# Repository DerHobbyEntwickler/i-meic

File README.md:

# i-meic

*(German version: [README_de.md](README_de.md))*

**The i-meic is a modular, expandable single-board computer based on the Intel 8088 CPU.**

> The hardware aims to recreate an IBM PC using the simplest possible means.
> The PC compute core consists of the 8088 CPU and 1 MB of main memory.
> All input/output is handled by a Raspberry Pi RP2040 Pro Micro.
> That is faster, simpler and cheaper than classic peripheral chips.

---

## What does "i-meic" mean?

The name is derived from the German description of the project:

| Letter | Meaning  |
|--------|-----------|
| **i** | (**i**)ntel 8088 |
| **m** | (**m**)odular|
| **e** | (**e**)xpandable |
| **i** | s(**i**)ngle-board |
| **c** | (**c**)omputer |

---

## Concept in brief

Classic 8088 systems require a large number of peripheral chips
(clock generator, bus drivers, interrupt controller, DMA, floppy/HDD
controller, video, keyboard, etc.). The i-meic replaces this entire set of
peripherals with **a single microcontroller**: the Raspberry Pi Pico.

**The PC compute core consists of:**

- **1× Intel 8088 CPU** (16-bit, 20 address lines)
- **2× SRAM of 512 KByte each** → together **1 MByte** (the maximum of the
  8088 address space)

**The Raspberry Pi RP2040 Pro Micro (ARM Cortex-M0+) takes care of:**

- **clock generation** for the 8088 CPU (single-step / clocked operation)
- **loading the BIOS** into SRAM at startup
- the **complete I/O processing** (every read/write access to an I/O port
  is intercepted and serviced by the Pico)
- the **serial connection** to a host PC (screen, keyboard and drives are
  virtualized over the console)
- the **ITP3 interface** for modular expansion

This architecture is unusually powerful because the Pico runs at a
significantly higher clock frequency than the historic 8088 peripherals and
can therefore handle I/O operations very quickly.

---

## System and data flow

This is how a runnable DOS computer is created from source code:

```
   ┌────────────────────────────────────────────────────────────────┐
   │  70_RON-BIOS-NASM …  BIOS.ASM  (8088 assembler, NASM)          │
   │        │  nasm -f bin                                          │
   │        ▼                                                       │
   │     BIOS.BIN  (pure 8088 binary BIOS, segment F800:0000)       │
   │        │  COM2INC  (see 60_FPC_Lazarus/25_LAZ_CLI64_COM2INC)   │
   │        ▼                                                       │
   │     BIOS.INC  (Pascal byte array  BIOS_ARR[…])                 │
   └────────┬───────────────────────────────────────────────────────┘
            │  gets embedded into the Pico firmware
            ▼
   ┌────────────────────────────────────────────────────────────────┐
   │  10_…/20_Lazarus_PICO…  Firmware (Free Pascal / RP2040)        │
   │        │  Lazarus / FPC                                        │
   │        ▼                                                       │
   │     imeic_dos.uf2   →   flash onto the Raspberry Pi Pico       │
   └────────┬───────────────────────────────────────────────────────┘
            │  Pico boots:
            │  1. loads BIOS_ARR into SRAM (F800:0000)
            │  2. clocks the 8088 CPU
            │  3. services all I/O requests (IORQ)
            ▼
   ┌────────────────────────────────────────────────────────────────┐
   │  i-meic board  (8088 + 2×512 KB SRAM)  ←── serial ───┐         │
   └──────────────────────────────────────────────────────┼─────────┘
                                                           │ UART 921600 Bd
   ┌───────────────────────────────────────────────────────▼────────┐
   │  60_…/20_LAZ_Console64 …  CONSOLE64  (host PC, Win64/Linux)    │
   │  provides screen, keyboard and drive images:                  │
   │    BOOTA.IMG  (1.44 MB floppy)     BOOTC.IMG  (8 MB hard disk) │
   └────────────────────────────────────────────────────────────────┘
```

---

## Repository structure

| Folder | Contents |
|--------|--------|
| [`10_i-meic-pico_V6/`](10_i-meic-pico_V6/) | The actual i-meic board: KiCAD hardware **and** Pico firmware (ARM cross-compiler, I/O interface for DOS) |
| [`10_i-meic-pico_V6/10_KiCAD/`](10_i-meic-pico_V6/10_KiCAD/) | KiCAD project, schematic, layout, Gerber data for PCB manufacturing |
| [`10_i-meic-pico_V6/20_Lazarus_PICO_i-meic-pico_V6_DOS/`](10_i-meic-pico_V6/20_Lazarus_PICO_i-meic-pico_V6_DOS/) | Source code of the Pico firmware for the **ARM cross-compiler** (Free Pascal / Lazarus). The I/O interface here is designed for **DOS**. |
| [`60_FPC_Lazarus/`](60_FPC_Lazarus/) | Host PC tools (Free Pascal / Lazarus) for Windows & Linux |
| [`60_FPC_Lazarus/20_LAZ_Console64_GUI64_Win64_Linux/`](60_FPC_Lazarus/20_LAZ_Console64_GUI64_Win64_Linux/) | **CONSOLE64** – terminal/console program for all i-meic (central tool) |
| [`60_FPC_Lazarus/25_LAZ_CLI64_COM2INC/`](60_FPC_Lazarus/25_LAZ_CLI64_COM2INC/) | **COM2INC** – command-line tool that converts a binary file into a Pascal/NASM include (byte array) |
| [`70_RON-BIOS-NASM_i-meic_WIN_Linux/`](70_RON-BIOS-NASM_i-meic_WIN_Linux/) | **RON-BIOS** – the 8088 BIOS in NASM assembler including build scripts |

>
> **Operating-system variants of the firmware:** For the **i-meic board**
> there are several firmware variants that differ only in the I/O interface –
> currently **DOS** (`…_DOS`) and **CP/M-86** (`…_CPM86`). The hardware and the
> ARM cross-compiler are identical in each case.

---

## Quick start

### 1. Have the PCB manufactured
The ready-to-use Gerber data is located at
`10_i-meic-pico_V6/10_KiCAD/gerber_i-meic-pico_V6.zip` and can be uploaded
directly to a PCB manufacturer. The schematic and layout for further
development are in the same folder as a KiCAD project.

### 2. Flash the Pico firmware
Copy `imeic_dos.uf2` onto the Raspberry Pi Pico (BOOTSEL mode).

### 3. Start the console and connect
Start `CONSOLE64` (in the folder
`60_FPC_Lazarus/20_LAZ_Console64_GUI64_Win64_Linux/bin/`), set the correct
COM port and 921600 baud, then power up the i-meic.

---

## Requirements

- **Hardware:** Intel 8088, 2× SRAM (512 KByte), Raspberry Pi Pico or a
  compatible RP2040 module (footprints for several variants are provided),
  serial connection to the host
- **Software (development):**
  - [KiCAD](https://www.kicad.org/) for the hardware
  - [Lazarus / Free Pascal](https://www.lazarus-ide.org/) including the
    **ARM cross-toolchain** for the RP2040 (the Pico is an ARM
    microcontroller); the firmware runs "bare-metal" on the Pico
  - RP2040 libraries by **Michael Ring** as a basis (included in the `units/`
    folder, **adapted for this project** – see the warning below), original:
    <https://github.com/michael-ring/pico-fpcexamples>
  - [NASM](https://www.nasm.us/) for the BIOS (binaries are included)

---

## Acknowledgements / third parties

- The Free Pascal libraries for the RP2040 come from **Michael Ring**:
  <https://github.com/michael-ring/pico-fpcexamples>. They were an
  **important basis** for this Pico/RP2040 variant.
  ⚠️ The libraries shipped in the `units/` folder have been **modified and
  adapted** for this project and **must not** be replaced by the current
  upstream version (otherwise compilation errors will occur).
- **NASM** is used to assemble the 8088 BIOS (see `LICENSE_NASM.TXT`).

---

## License

This project is licensed under the **GNU General Public License v3.0** – see
[`LICENSE`](LICENSE). The BIOS and COM2INC additionally include the NASM
license (`LICENSE_NASM.TXT`) for the bundled NASM binaries.

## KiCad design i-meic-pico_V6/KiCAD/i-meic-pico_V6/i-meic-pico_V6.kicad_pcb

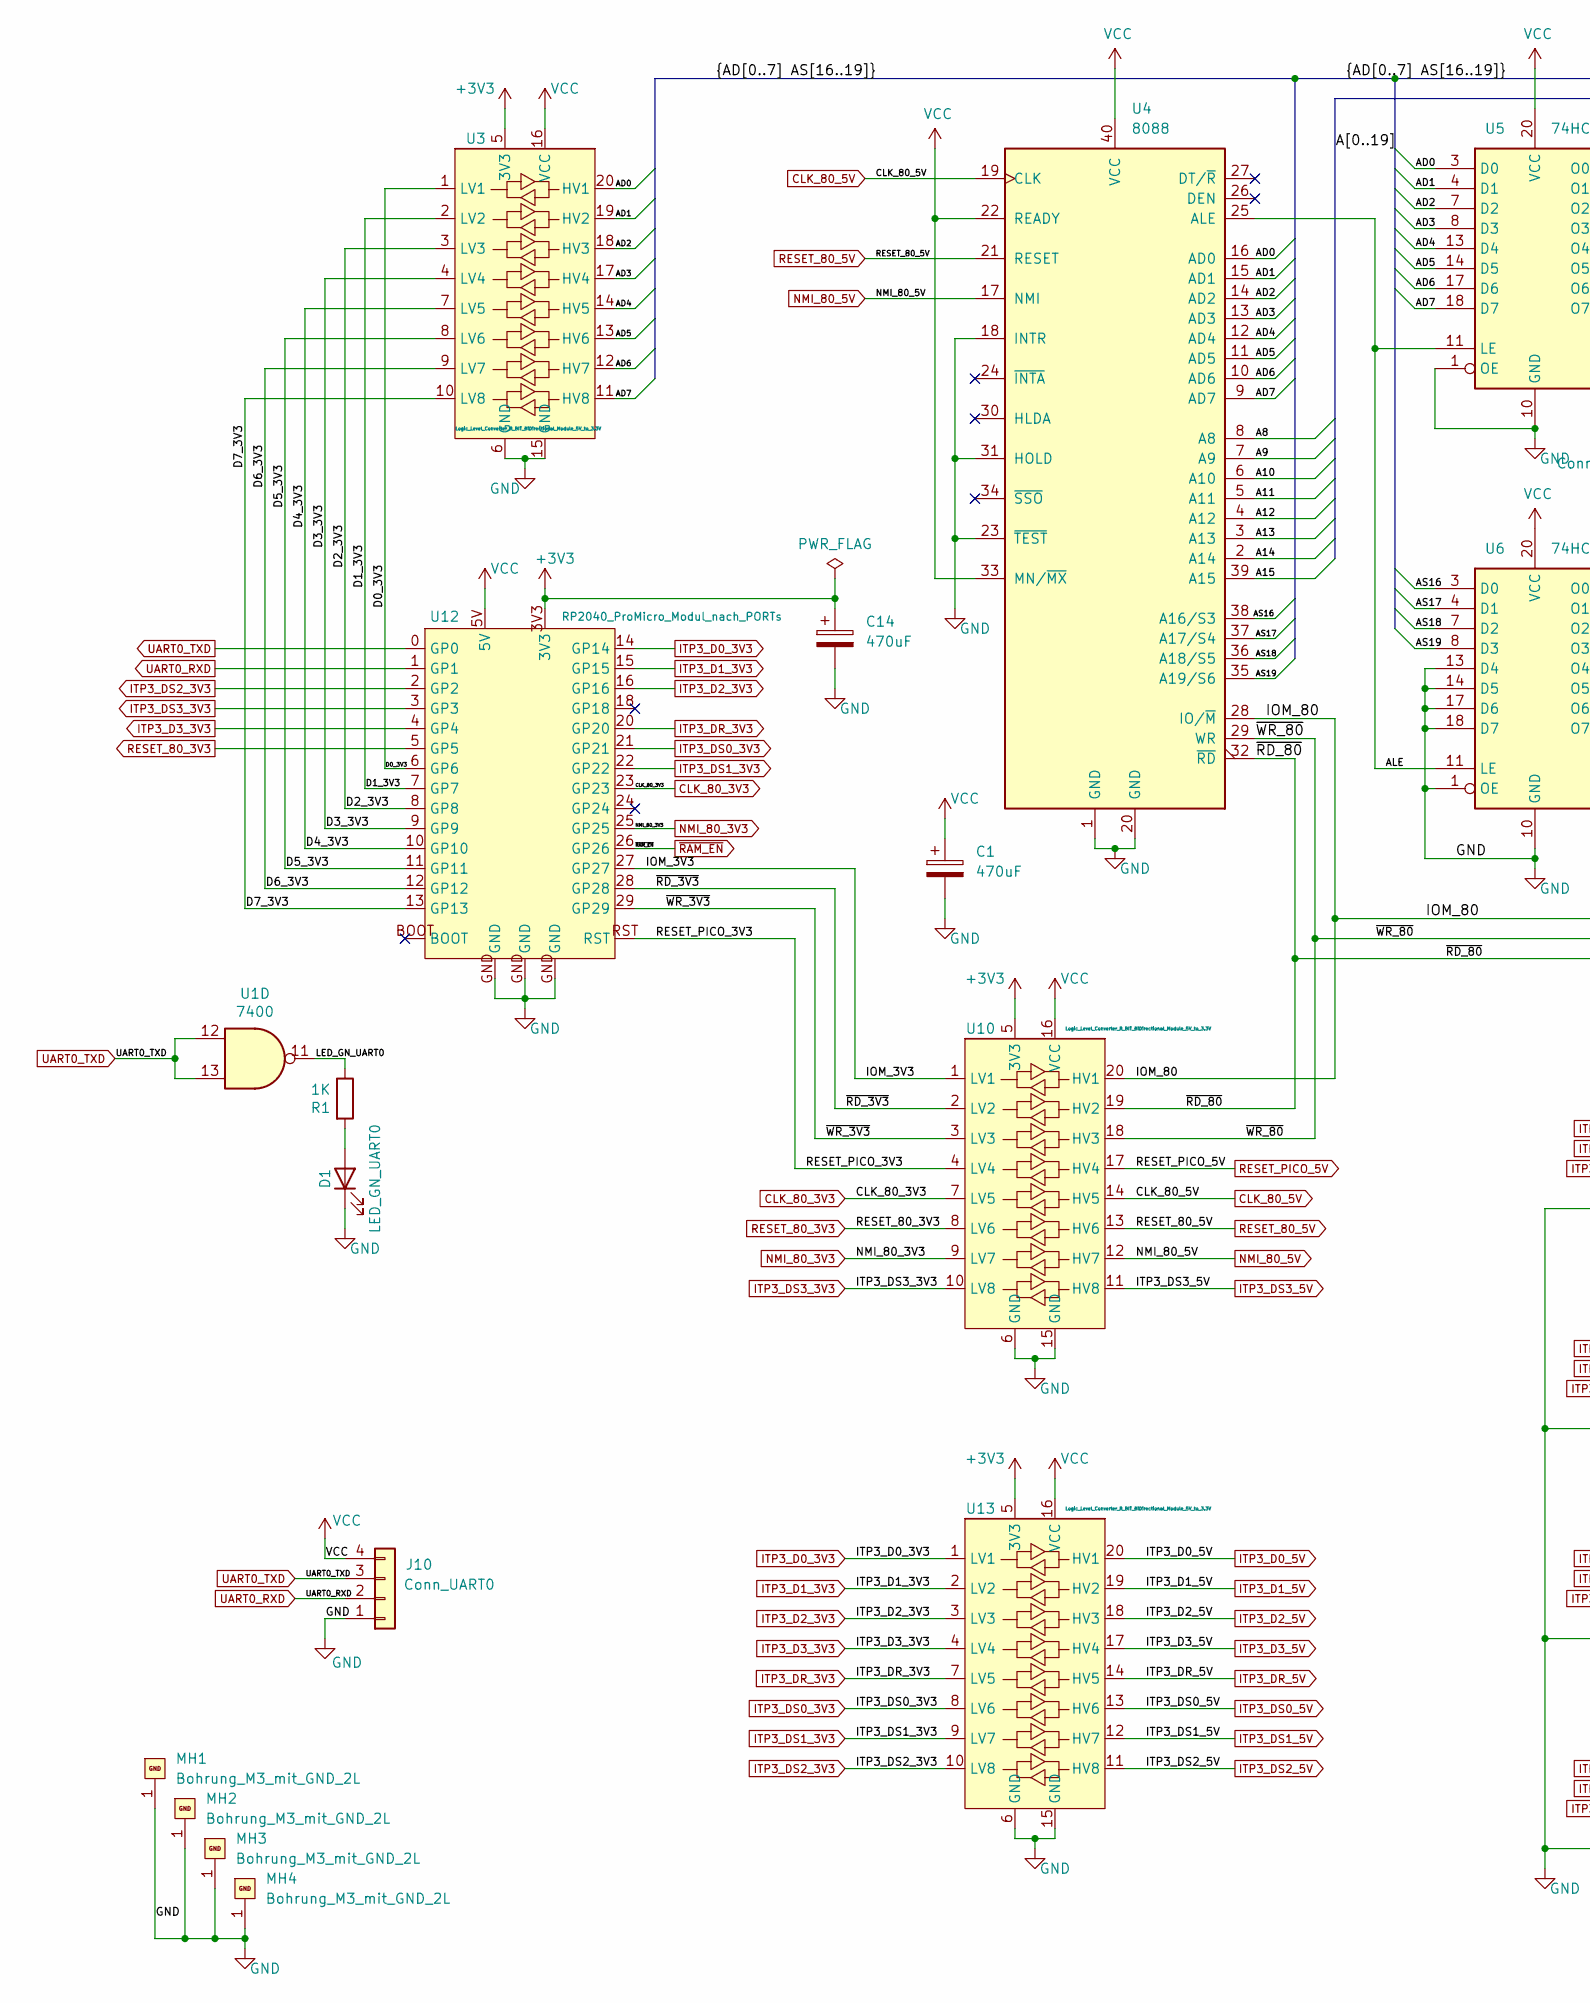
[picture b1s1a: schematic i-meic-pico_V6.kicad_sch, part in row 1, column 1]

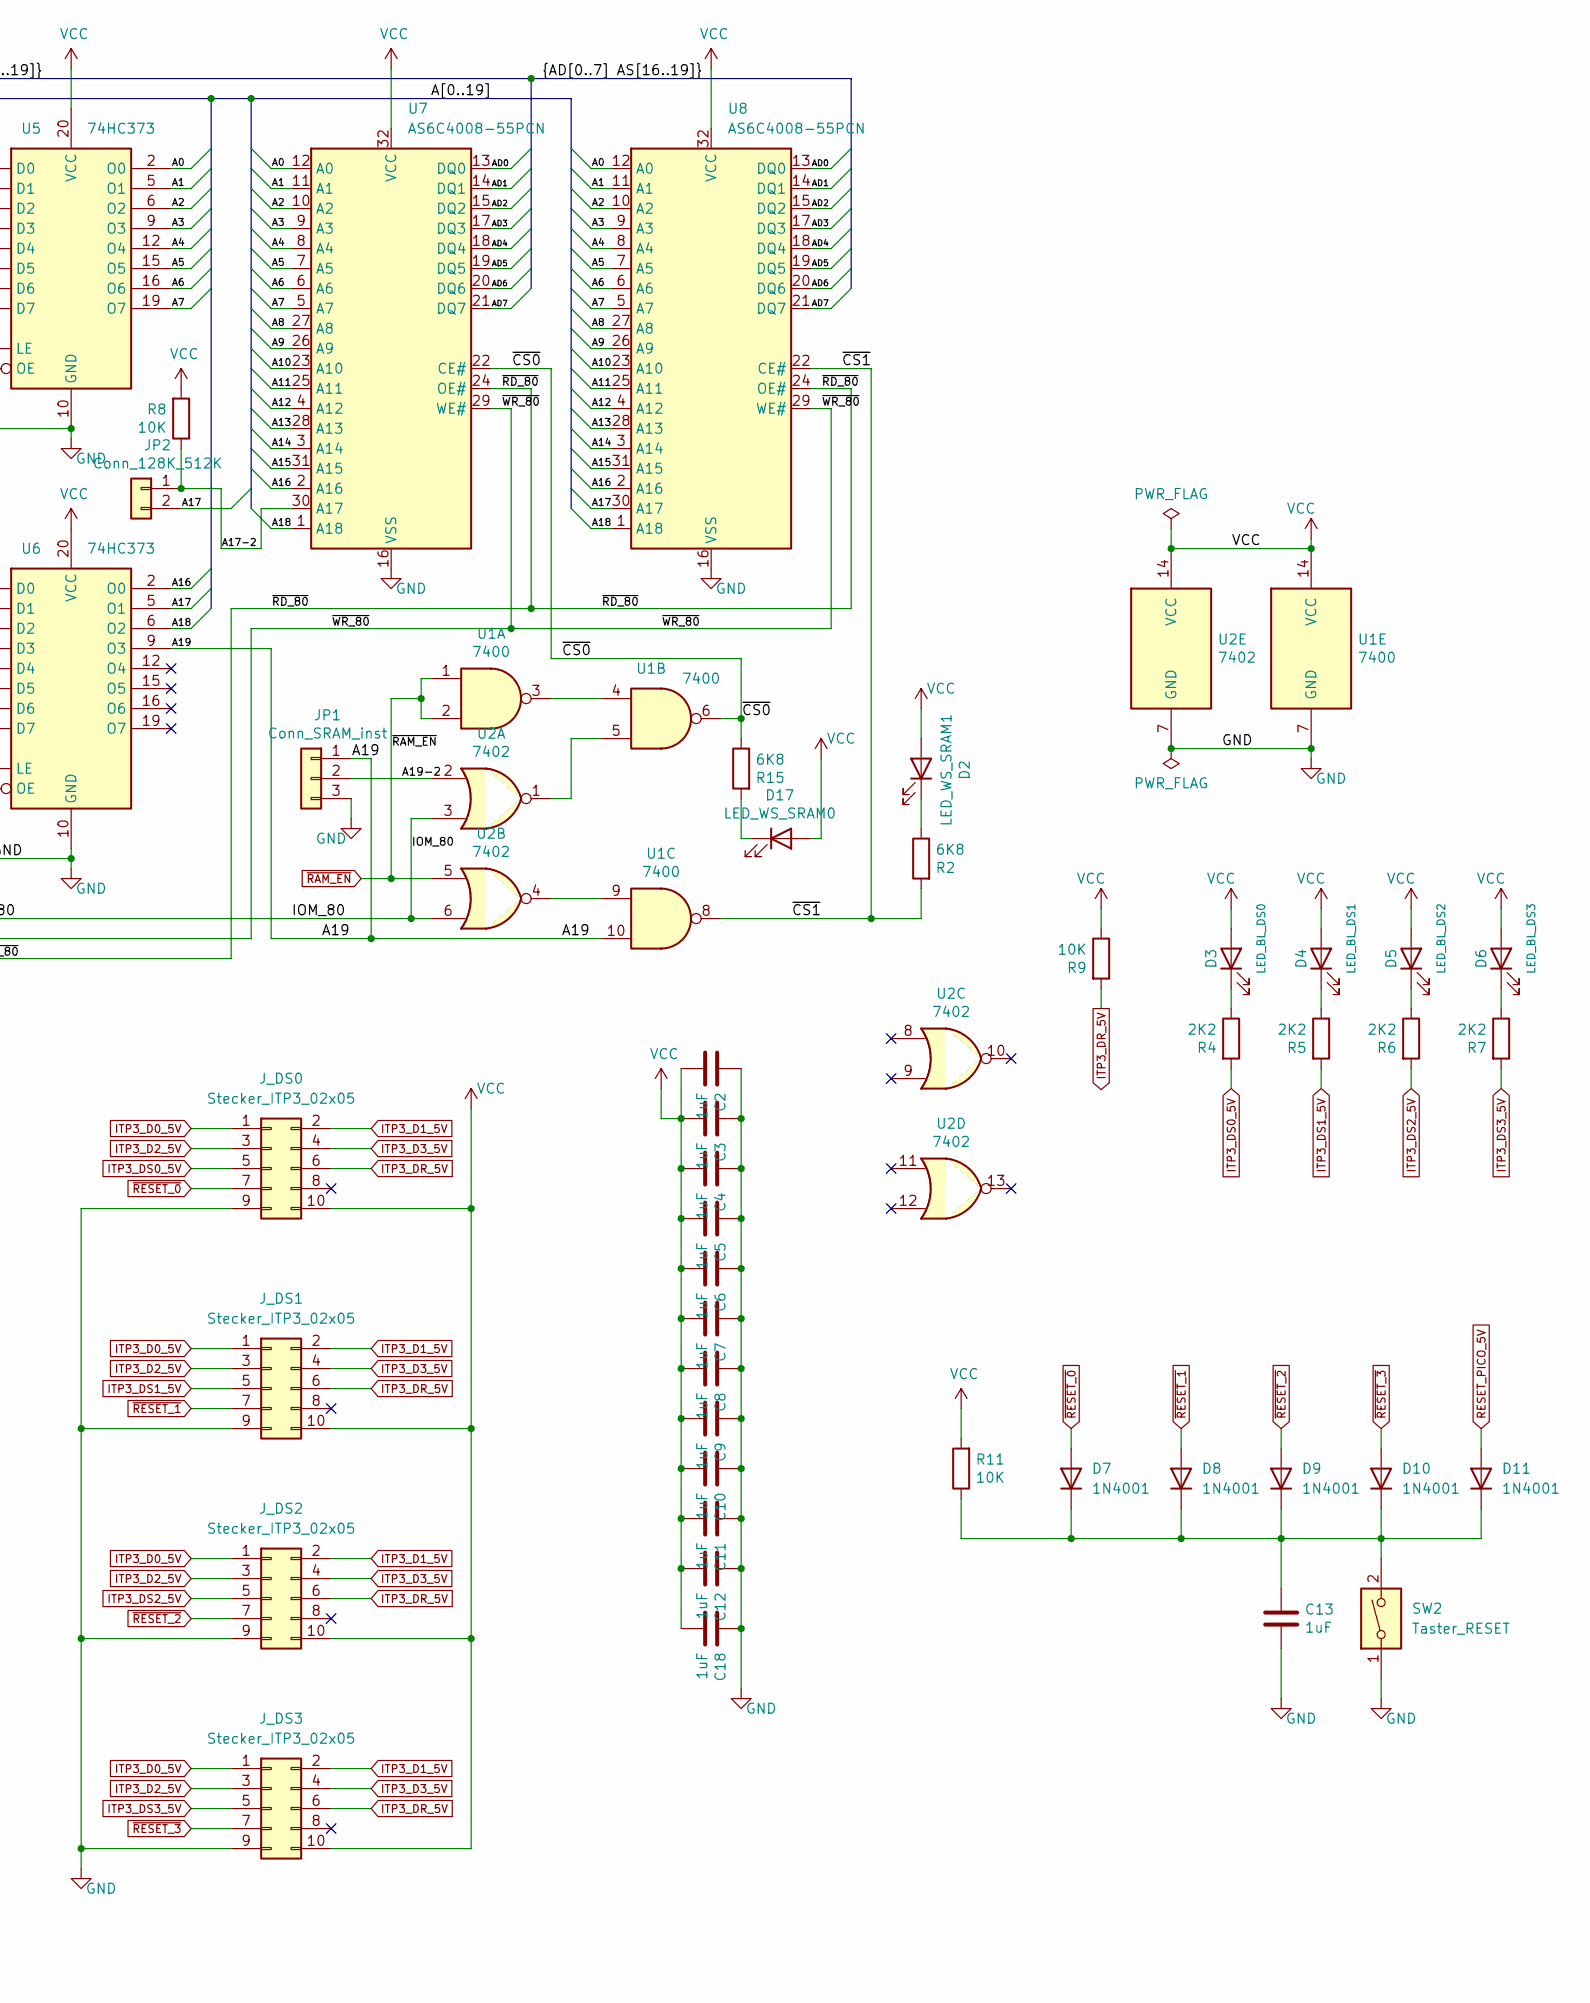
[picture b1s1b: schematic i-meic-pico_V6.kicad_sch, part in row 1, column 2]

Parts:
C1, C14: 470uF; CP_470uF_Radial_D8.0mm_P3.50mm
C2, C3, C4, C5, C6, C7, C8, C9, C10, C11, C12, C13, C18: 1uF; C_Disc_D5.0mm_W2.5mm_P5.00mm_2
D1: LED_GN_UART0; LED_D3.0mm
D2: LED_WS_SRAM1; LED_D3.0mm
D3: LED_BL_DS0; LED_D3.0mm
D4: LED_BL_DS1; LED_D3.0mm
D5: LED_BL_DS2; LED_D3.0mm
D6: LED_BL_DS3; LED_D3.0mm
D7, D8, D9, D10, D11: 1N4001; Diode_1N4001
D17: LED_WS_SRAM0; LED_D3.0mm
J10: Conn_UART0; PinHeader_1x04_P2.54mm_Vertical
JP1: Conn_SRAM_inst; PinHeader_1x03_P2.54mm_Vertical
JP2: Conn_128K_512K; PinHeader_1x02_P2.54mm_Vertical
J_DS0, J_DS1, J_DS2, J_DS3: Stecker_ITP3_02x05; Stecker_ITP3_2x05_RM_2.54mm_Vertical
MH1, MH2, MH3, MH4: Bohrung_M3_mit_GND_2L; Bohrung_M3_mit_GND
R1: 1K; R_Axial_DIN0204_L3.6mm_D1.6mm_P7.62mm_Horizontal
R2, R15: 6K8; R_Axial_DIN0204_L3.6mm_D1.6mm_P7.62mm_Horizontal
R4, R5, R6, R7: 2K2; R_Axial_DIN0204_L3.6mm_D1.6mm_P7.62mm_Horizontal
R8, R9, R11: 10K; R_Axial_DIN0204_L3.6mm_D1.6mm_P7.62mm_Horizontal
SW2: Taster_RESET; Schalter_Taster_PUSH-12,55mm_und_6,5mm
U1: 7400; DIP-14_W7.62mm
U2: 7402; DIP-14_W7.62mm
U3, U10, U13: Logic_Level_Converter_8_BIT_BiDirectional_Module_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; Logic_Level_Converter_8Bit_BiDirectional_Module_5V_to_3.3V
U4: 8088; DIP-40_W15.24mm
U5, U6: 74HC373; DIP-20_W7.62mm
U7, U8: AS6C4008-55PCN; DIP-32_W15.24mm
U12: RP2040_ProMicro_Modul_nach_PORTs; RP2040_ProMicro_Modul

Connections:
+3V3: C14.1, U3.5 (3V3), U10.5 (3V3), U12.3V3, U13.5 (3V3)
/A0: U5.2 (O0), U7.12 (A0), U8.12 (A0)
/A1: U5.5 (O1), U7.11 (A1), U8.11 (A1)
/A2: U5.6 (O2), U7.10 (A2), U8.10 (A2)
/A3: U5.9 (O3), U7.9 (A3), U8.9 (A3)
/A4: U5.12 (O4), U7.8 (A4), U8.8 (A4)
/A5: U5.15 (O5), U7.7 (A5), U8.7 (A5)
/A6: U5.16 (O6), U7.6 (A6), U8.6 (A6)
/A7: U5.19 (O7), U7.5 (A7), U8.5 (A7)
/A8: U4.8 (A8), U7.27 (A8), U8.27 (A8)
/A9: U4.7 (A9), U7.26 (A9), U8.26 (A9)
/A10: U4.6 (A10), U7.23 (A10), U8.23 (A10)
/A11: U4.5 (A11), U7.25 (A11), U8.25 (A11)
/A12: U4.4 (A12), U7.4 (A12), U8.4 (A12)
/A13: U4.3 (A13), U7.28 (A13), U8.28 (A13)
/A14: U4.2 (A14), U7.3 (A14), U8.3 (A14)
/A15: U4.39 (A15), U7.31 (A15), U8.31 (A15)
/A16: U6.2 (O0), U7.2 (A16), U8.2 (A16)
/A17: JP2.2, U6.5 (O1), U8.30 (A17)
/A17-2: JP2.1, R8.1, U7.30 (A17)
/A18: U6.6 (O2), U7.1 (A18), U8.1 (A18)
/A19: JP1.1, U1.10, U6.9 (O3)
/A19-2: JP1.2, U2.2
/AD0: U3.20 (HV1), U4.16 (AD0), U5.3 (D0), U7.13 (DQ0), U8.13 (DQ0)
/AD1: U3.19 (HV2), U4.15 (AD1), U5.4 (D1), U7.14 (DQ1), U8.14 (DQ1)
/AD2: U3.18 (HV3), U4.14 (AD2), U5.7 (D2), U7.15 (DQ2), U8.15 (DQ2)
/AD3: U3.17 (HV4), U4.13 (AD3), U5.8 (D3), U7.17 (DQ3), U8.17 (DQ3)
/AD4: U3.14 (HV5), U4.12 (AD4), U5.13 (D4), U7.18 (DQ4), U8.18 (DQ4)
/AD5: U3.13 (HV6), U4.11 (AD5), U5.14 (D5), U7.19 (DQ5), U8.19 (DQ5)
/AD6: U3.12 (HV7), U4.10 (AD6), U5.17 (D6), U7.20 (DQ6), U8.20 (DQ6)
/AD7: U3.11 (HV8), U4.9 (AD7), U5.18 (D7), U7.21 (DQ7), U8.21 (DQ7)
/ALE: U4.25 (ALE), U5.11 (LE), U6.11 (LE)
/AS16: U4.38 (A16/S3), U6.3 (D0)
/AS17: U4.37 (A17/S4), U6.4 (D1)
/AS18: U4.36 (A18/S5), U6.7 (D2)
/AS19: U4.35 (A19/S6), U6.8 (D3)
/D0_3V3: U3.1 (LV1), U12.6 (GP6)
/D1_3V3: U3.2 (LV2), U12.7 (GP7)
/D2_3V3: U3.3 (LV3), U12.8 (GP8)
/D3_3V3: U3.4 (LV4), U12.9 (GP9)
/D4_3V3: U3.7 (LV5), U12.10 (GP10)
/D5_3V3: U3.8 (LV6), U12.11 (GP11)
/D6_3V3: U3.9 (LV7), U12.12 (GP12)
/D7_3V3: U3.10 (LV8), U12.13 (GP13)
/IOM_3V3: U10.1 (LV1), U12.27 (GP27)
/IOM_80: U2.3, U2.6, U4.28 (IO/~M), U10.20 (HV1)
/LED_GN_UART0: R1.1, U1.11
/RESET_PICO_3V3: U10.4 (LV4), U12.RST
/~CS0: R15.1, U1.6, U7.22 (CE#)
/~CS1: R2.2, U1.8, U8.22 (CE#)
/~RD_3V3: U10.2 (LV2), U12.28 (GP28)
/~RD_80: U4.32 (~RD), U7.24 (OE#), U8.24 (OE#), U10.19 (HV2)
/~WR_3V3: U10.3 (LV3), U12.29 (GP29)
/~WR_80: U4.29 (WR), U7.29 (WE#), U8.29 (WE#), U10.18 (HV3)
CLK_80_3V3: U10.7 (LV5), U12.23 (GP23)
CLK_80_5V: U4.19 (CLK), U10.14 (HV5)
GND: C1.2, C2.1, C3.1, C4.1, C5.1, C6.1, C7.1, C8.1, C9.1, C10.1, C11.1, C12.1, C13.2, C14.2, C18.1, D1.1 (K), J10.1, JP1.3, J_DS0.9, J_DS1.9, J_DS2.9, J_DS3.9, MH1.1 (GND), MH2.1 (GND), MH3.1 (GND), MH4.1 (GND), SW2.1, U1.7 (GND), U2.7 (GND), U3.6 (GND), U3.15 (GND), U4.1 (GND), U4.18 (INTR), U4.20 (GND), U4.23 (~TEST), U4.31 (HOLD), U5.1 (OE), U5.10 (GND), U6.1 (OE), U6.10 (GND), U6.13 (D4), U6.14 (D5), U6.17 (D6), U6.18 (D7), U7.16 (VSS), U8.16 (VSS), U10.6 (GND), U10.15 (GND), U12.GND, U13.6 (GND), U13.15 (GND)
ITP3_D0_3V3: U12.14 (GP14), U13.1 (LV1)
ITP3_D0_5V: J_DS0.1, J_DS1.1, J_DS2.1, J_DS3.1, U13.20 (HV1)
ITP3_D1_3V3: U12.15 (GP15), U13.2 (LV2)
ITP3_D1_5V: J_DS0.2, J_DS1.2, J_DS2.2, J_DS3.2, U13.19 (HV2)
ITP3_D2_3V3: U12.16 (GP16), U13.3 (LV3)
ITP3_D2_5V: J_DS0.3, J_DS1.3, J_DS2.3, J_DS3.3, U13.18 (HV3)
ITP3_D3_3V3: U12.4 (GP4), U13.4 (LV4)
ITP3_D3_5V: J_DS0.4, J_DS1.4, J_DS2.4, J_DS3.4, U13.17 (HV4)
ITP3_DR_3V3: U12.20 (GP20), U13.7 (LV5)
ITP3_DR_5V: J_DS0.6, J_DS1.6, J_DS2.6, J_DS3.6, R9.2, U13.14 (HV5)
ITP3_DS0_3V3: U12.21 (GP21), U13.8 (LV6)
ITP3_DS0_5V: J_DS0.5, R4.2, U13.13 (HV6)
ITP3_DS1_3V3: U12.22 (GP22), U13.9 (LV7)
ITP3_DS1_5V: J_DS1.5, R5.2, U13.12 (HV7)
ITP3_DS2_3V3: U12.2 (GP2), U13.10 (LV8)
ITP3_DS2_5V: J_DS2.5, R6.2, U13.11 (HV8)
ITP3_DS3_3V3: U10.10 (LV8), U12.3 (GP3)
ITP3_DS3_5V: J_DS3.5, R7.2, U10.11 (HV8)
NMI_80_3V3: U10.9 (LV7), U12.25 (GP25)
NMI_80_5V: U4.17 (NMI), U10.12 (HV7)
unnamed: D1.2 (A), R1.2
unnamed: D2.1 (K), R2.1
unnamed: D3.1 (K), R4.1
unnamed: D4.1 (K), R5.1
unnamed: D5.1 (K), R6.1
unnamed: D6.1 (K), R7.1
unnamed: C13.1, D7.1 (K), D8.1 (K), D9.1 (K), D10.1 (K), D11.1 (K), R11.1, SW2.2
unnamed: D17.1 (K), R15.2
unnamed: U1.3, U1.4
unnamed: U1.5, U2.1
unnamed: U1.9, U2.4
RESET_80_3V3: U10.8 (LV6), U12.5 (GP5)
RESET_80_5V: U4.21 (RESET), U10.13 (HV6)
RESET_PICO_5V: D11.2 (A), U10.17 (HV4)
UART0_RXD: J10.2, U12.1 (GP1)
UART0_TXD: J10.3, U1.12, U1.13, U12.0 (GP0)
VCC: C1.1, C2.2, C3.2, C4.2, C5.2, C6.2, C7.2, C8.2, C9.2, C10.2, C11.2, C12.2, C18.2, D2.2 (A), D3.2 (A), D4.2 (A), D5.2 (A), D6.2 (A), D17.2 (A), J10.4, J_DS0.10, J_DS1.10, J_DS2.10, J_DS3.10, R8.2, R9.1, R11.2, U1.14 (VCC), U2.14 (VCC), U3.16 (VCC), U4.22 (READY), U4.33 (MN/~MX), U4.40 (VCC), U5.20 (VCC), U6.20 (VCC), U7.32 (VCC), U8.32 (VCC), U10.16 (VCC), U12.5V, U13.16 (VCC)
~RAM_EN: U1.1, U1.2, U2.5, U12.26 (GP26)
~RESET_0: D7.2 (A), J_DS0.7
~RESET_1: D8.2 (A), J_DS1.7
~RESET_2: D9.2 (A), J_DS2.7
~RESET_3: D10.2 (A), J_DS3.7

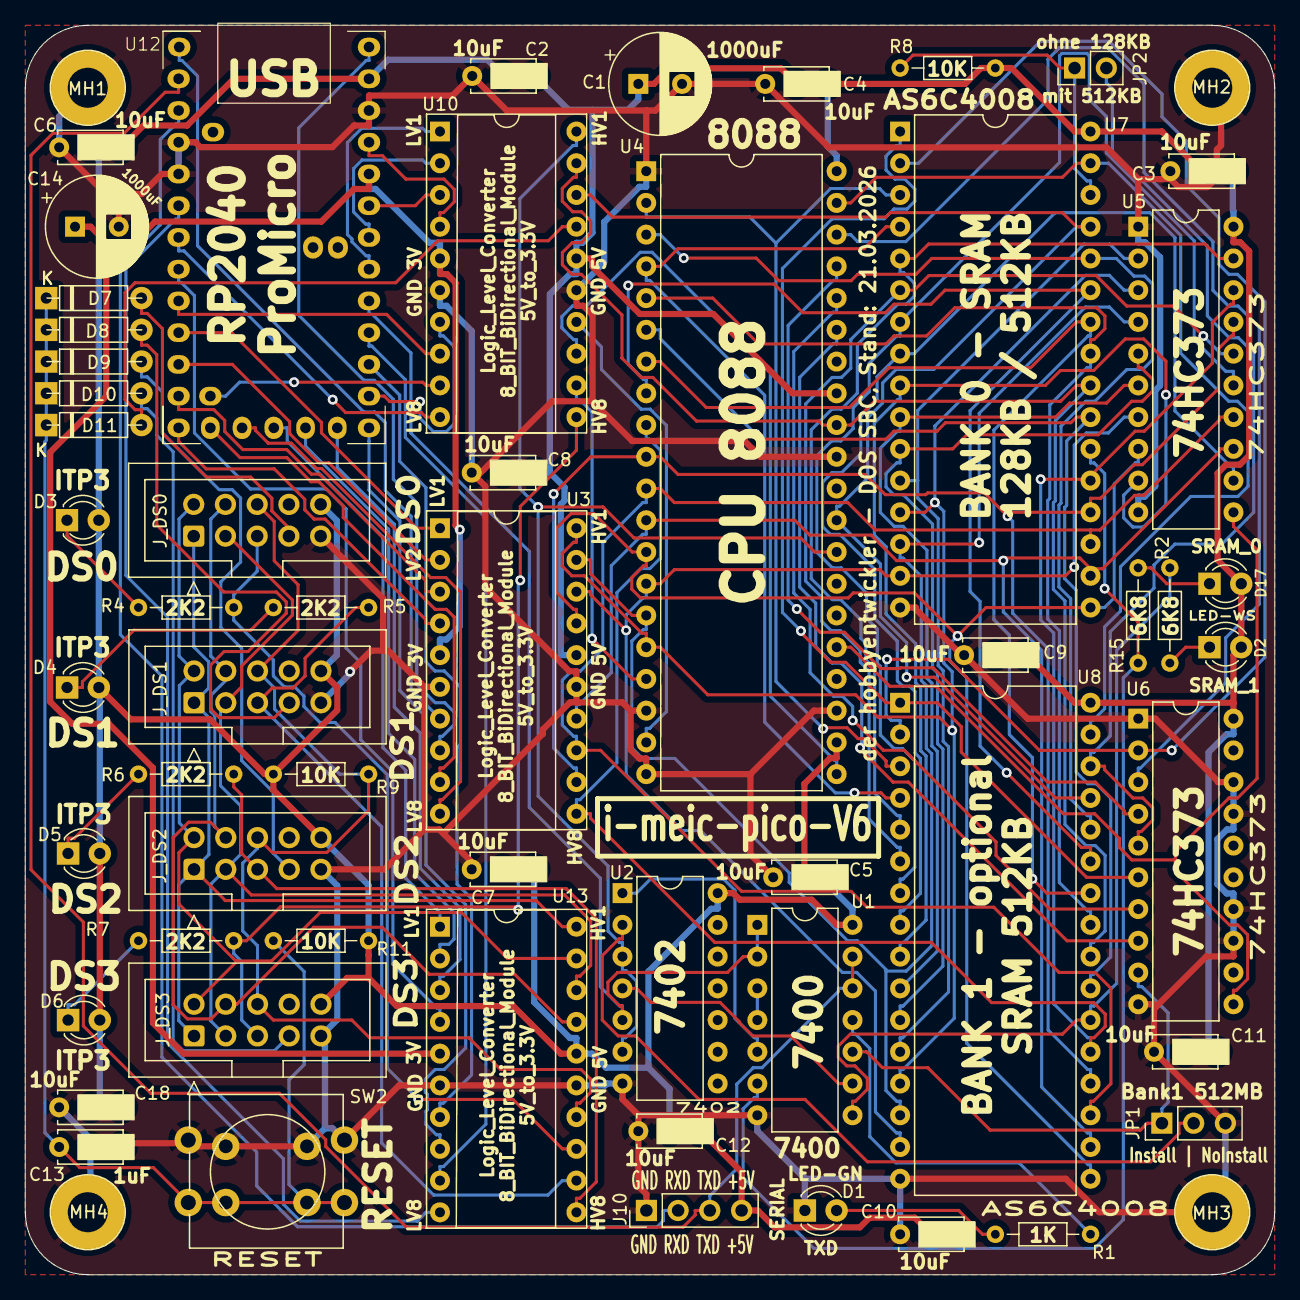
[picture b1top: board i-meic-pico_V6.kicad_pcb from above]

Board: 2 copper layers, 100.0 x 100.0 mm, 60 parts (0 on the bottom side), 99 nets.

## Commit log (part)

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2026-06-28 Änderungen am 28.06.2026
2026-06-28 change 28.06.2026 V2
2026-06-28 change 28.06.2026 V4
2026-06-28 change 28.06.2026 V5
2026-06-28 change 28.06.20026 14:52
2026-06-28 update 28.06.2026 V6
2026-06-28 update 28.06.2026 20:00
2026-06-29 change 290626 1143
2026-06-29 changes 290626 11:53
2026-06-29 change 290626 1410
